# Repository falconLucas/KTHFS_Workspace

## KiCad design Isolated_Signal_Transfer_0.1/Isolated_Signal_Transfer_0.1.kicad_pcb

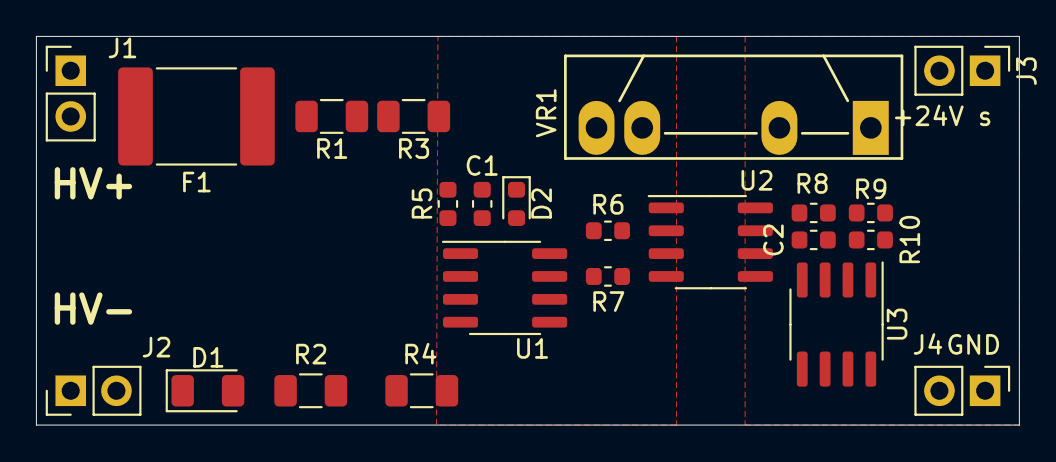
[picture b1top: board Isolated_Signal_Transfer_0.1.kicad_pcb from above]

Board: 2 copper layers, 54.6 x 21.6 mm, 23 parts (0 on the bottom side), 17 nets, no tracks yet.

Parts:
C1, C2: 10n; C_0603_1608Metric
D1: D_Schottky; D_1206_3216Metric
D2: 5V; D_0603_1608Metric
F1: Fuse; Fuse_2920_7451Metric
J1, J2, J3, J4: Conn_01x02_Male; PinHeader_1x02_P2.54mm_Vertical
R1, R2, R3, R4: 2M; R_1206_3216Metric
R5: 100K; R_0603_1608Metric
R6: 2K; R_0603_1608Metric
R7, R8: 10K; R_0603_1608Metric
R9, R10: 5K; R_0603_1608Metric
U1, U3: LM358; SOIC-8_3.9x4.9mm_P1.27mm
U2: IL300; SOIC-8_3.9x4.9mm_P1.27mm
VR1: Wurth-FISM; SIP4_Sharp-SSR_P7.62mm_Straight

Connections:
+5Viso: U1.5, U1.8, U2.3, VR1.3
+24V: J3.2, U2.6, U3.5, U3.8, VR1.1
GND: C2.2, J4.1, J4.2, R8.2, R9.2, U3.4, U3.6, VR1.2
GNDiso: C1.2, D2.2, R4.1, R5.2, R7.2, U1.4, U1.6, U2.1, VR1.4
unnamed: C1.1, D2.1, R3.1, R5.1, U1.3
unnamed: C2.1, R8.1, U2.5, U3.3
unnamed: D1.1, J2.1, J2.2
unnamed: D1.2, R2.2
unnamed: F1.1, R1.2
unnamed: F1.2, J1.1, J1.2
unnamed: J3.1, R10.1, U3.1
unnamed: R1.1, R3.2
unnamed: R2.1, R4.2
unnamed: R6.1, U1.1
unnamed: R6.2, U2.2
unnamed: R7.1, U1.2, U2.4
unnamed: R9.1, R10.2, U3.2

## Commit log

2019-09-06 Precharge
    Adding KiCad Files for next generation precharge
